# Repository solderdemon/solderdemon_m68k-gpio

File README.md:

# SolderDemon m68k GPIO

## Overview

A SolderDemon m68k expansion card with 32 GPIO lines at 5 V logic levels in four 8-bit ports. Two right-angle headers expose the signals, and three ATF1502AS CPLDs handle bus decoding and port control.

J1 matches the expansion bus pinout of [rosco_m68k r2](https://github.com/rosco-m68k/rosco_m68k). The original rosco_m68k project was created by Ross Bamford, The Really Old-School Company Limited, and contributors.

**Status.** r1 fabrication files and CPLD programming files are available. Hardware verification is pending.

## Start here

- [KiCad project](design/solderdemon_m68k-gpio.kicad_pro)
- [Schematic (PDF)](manufacturing/solderdemon_m68k-gpio-schematic.pdf)
- [Assembly and bring-up](docs/BRINGUP.md)
- [Gerbers and drill files](manufacturing/solderdemon_m68k-gpio-fab.zip)

## Board views

| Top | Bottom |
|:---:|:---:|
|  |  |

## Hardware

### Features

| | |
|---|---|
| Registers | `$F40001` A, `$F40003` B, `$F40005` direction, `$F40007` C, `$F40009` D; byte access only |
| Logic | 3 × ATF1502AS-10JU44 in PLCC-44 sockets, programmed in one J4 JTAG chain; BAT85 diode for DTACK |
| Ports | registered CPLD outputs, tristated by the direction register; readback senses the header pins |
| Direction | per 8-pin port |
| Pull-ups | 10 kΩ on every pin (4 × SIP-9 arrays) |
| Power | 5 V from the bus |
| Assembly | through-hole only, 3 × PLCC-44 sockets, CPLDs need JEDEC files and a JTAG programmer |
| Size | 86 × 96 mm, 2 layers |

### J2 / J3 connectors

Two right-angle, unshrouded 2×10 pin headers, 2.54 mm pitch, in the original connector positions on the left edge. J2 is above J3. Pin 1 is marked on the PCB.

| Pins | J2 | J3 |
|---|---|---|
| 1–8 | A0–A7 (driver bits 0–7) | C0–C7 (bits 16–23) |
| 9–16 | B0–B7 (bits 8–15) | D0–D7 (bits 24–31) |
| 17, 19, 20 | GND | GND |
| 18 | +5V from the bus, no fuse | +5V from the bus, no fuse |

All VCC pins of U1–U3 connect to the bus +5 V rail. The CPLD output drive differs from the previous 74HCT574; size external loads to the ATF1502AS datasheet. The unshrouded headers have no key; check cable orientation before connecting an adapter.

### Registers

| Address | Write | Read |
|---|---|---|
| `$F40001` | port A output latch | port A pin levels |
| `$F40003` | port B output latch | port B pin levels |
| `$F40005` | direction: b0 A, b1 B, b2 C, b3 D; 1 = output | — |
| `$F40007` | port C output latch | port C pin levels |
| `$F40009` | port D output latch | port D pin levels |

System reset clears the direction register, so every pin starts as an input. Every byte (odd-address) cycle in `$F40000–$F41FFF` gets DTACK; unused addresses read as garbage, and even-address access ends in a bus error.

## Using the board

### Example

```c
#include "gpio.h"

gpio_init();                                        /* all inputs, latches 0 */
gpio_config(GPIO_DIR_A | GPIO_DIR_C, 0x00000000);   /* A and C outputs (low), B and D inputs */
gpio_write_pin(16, true);                           /* J3.1 (C0) = 5 V */
uint32_t in = gpio_read();                          /* B in bits 8..15, D in bits 24..31 */
```

`gpio_selftest()` drives every pin with test patterns and returns a mask of failed pins; run it with J2 and J3 disconnected.

`gpio_write_port(port, value)` and `gpio_read_port(port)` touch one 8-bit port (0..3 = A..D) with a single register access and leave the other ports alone.

For a PS/2 keyboard and mouse on J2 or J3, see the [GPIO PS/2 adapter](https://github.com/solderdemon/solderdemon_m68k-gpio-ps2).

## Build and verification

### Design files

| Path | Contents |
|---|---|
| `design/solderdemon_m68k-gpio.kicad_pro` / `.kicad_sch` / `.kicad_pcb` | KiCad 10 project |
| `solderdemon_m68k-gpio.kicad_sym`, `solderdemon_m68k-gpio.pretty/` | local CPLD/bus symbols, the J1 socket footprint and the SolderDemon logo |
| `code/firmware/cpld/gpio_decode.pld`, `gpio_ab.pld`, `gpio_cd.pld`, `build.sh` | ATF1502AS logic, pinouts and JEDEC builds |
| `logo.png` | logo source; `tools/make_logo.py` turns it into `SolderDemon_Logo` (same generator and size as on the busboard) |
| `manufacturing/` | r1 Gerbers, drill, fab zip, pos, BOM and schematic PDF |
| `code/software/` | driver `gpio.c/.h`, example `main.c`, Makefile |
| `code/tests/test_driver.c` | driver test against a model of the latches, direction register and pull-ups |
| `tools/build_card.py`, `tools/make_bus_footprint.py`, `tools/make_logo.py`, `tools/route_card.py`, `tools/cleanup_dangling.py` | schematic/PCB generation, J1 footprint, routing, router clean-up |
| `tools/cupl.py`, `tools/sim_card.py` | CUPL source interpreter and GPIO behavior checks |
| [docs/DESIGN.md](docs/DESIGN.md) | how the card works: addressing, bus cycles, DTACK diode, levels, power |
| [docs/TIMING.md](docs/TIMING.md) | worst-case bus timing against the MC68010 at 10 MHz, /DTACK level |
| [docs/BRINGUP.md](docs/BRINGUP.md) | assembly and first power-up |
| [docs/BUILD.md](docs/BUILD.md) | regenerating the files |

### Verification

- r1 schematic ERC: 0 violations; schematic/PCB parity: 0 issues.
- All three CPLD sources fit successfully with locked pins and JEDEC output (decoder 11/32 macrocells, each port CPLD 27/32). CUPL source simulation passes address decode, writes, reset and pin readback. ERC: 0 violations. Routed DRC: 0 violations, 0 unconnected pads, 0 schematic parity issues; 123 vias. Worst-case timing at 10 MHz: reads with zero wait states (/DTACK margin 75 ns, data margin 167 ns), writes with at most one; see docs/TIMING.md. The driver test models the register interface, but it does not verify the new CPLD fuse maps.
- Physical board and /DTACK level on an oscilloscope remain unverified.

<!-- repository-layout -->
## Repository layout

- [`design/`](design/solderdemon_m68k-gpio.kicad_pro): KiCad project, schematic sheets, PCB, local libraries and design data. Open the project directly here.
- [`code/firmware/`](code/firmware/): ROM and programmable-logic sources and programming files.
- [`code/software/`](code/software/): drivers, examples and applications.
- [`code/build/`](code/build/): local build products; ignored by Git except for its README.
- [`tools/`](tools/): generators, simulations and export scripts. Run commands from the repository root unless stated otherwise.
- [`manufacturing/`](manufacturing/): fabrication packages.

Programmable-logic files are in `code/firmware/cpld/`. Native CPLD tools retain their adjacent `bin/` outputs.
Design files and documentation are generated by scripts in `tools/`; change the sources and regenerate. Keep `.kicad_pro` as the source of DRC rules.
<!-- /repository-layout -->

## Licences and attribution

Copyright © 2026 SolderDemon.

No project-wide licence has been specified.

Hardware and driver by Mykhailo.

Third-party materials retain their original notices and licence terms.

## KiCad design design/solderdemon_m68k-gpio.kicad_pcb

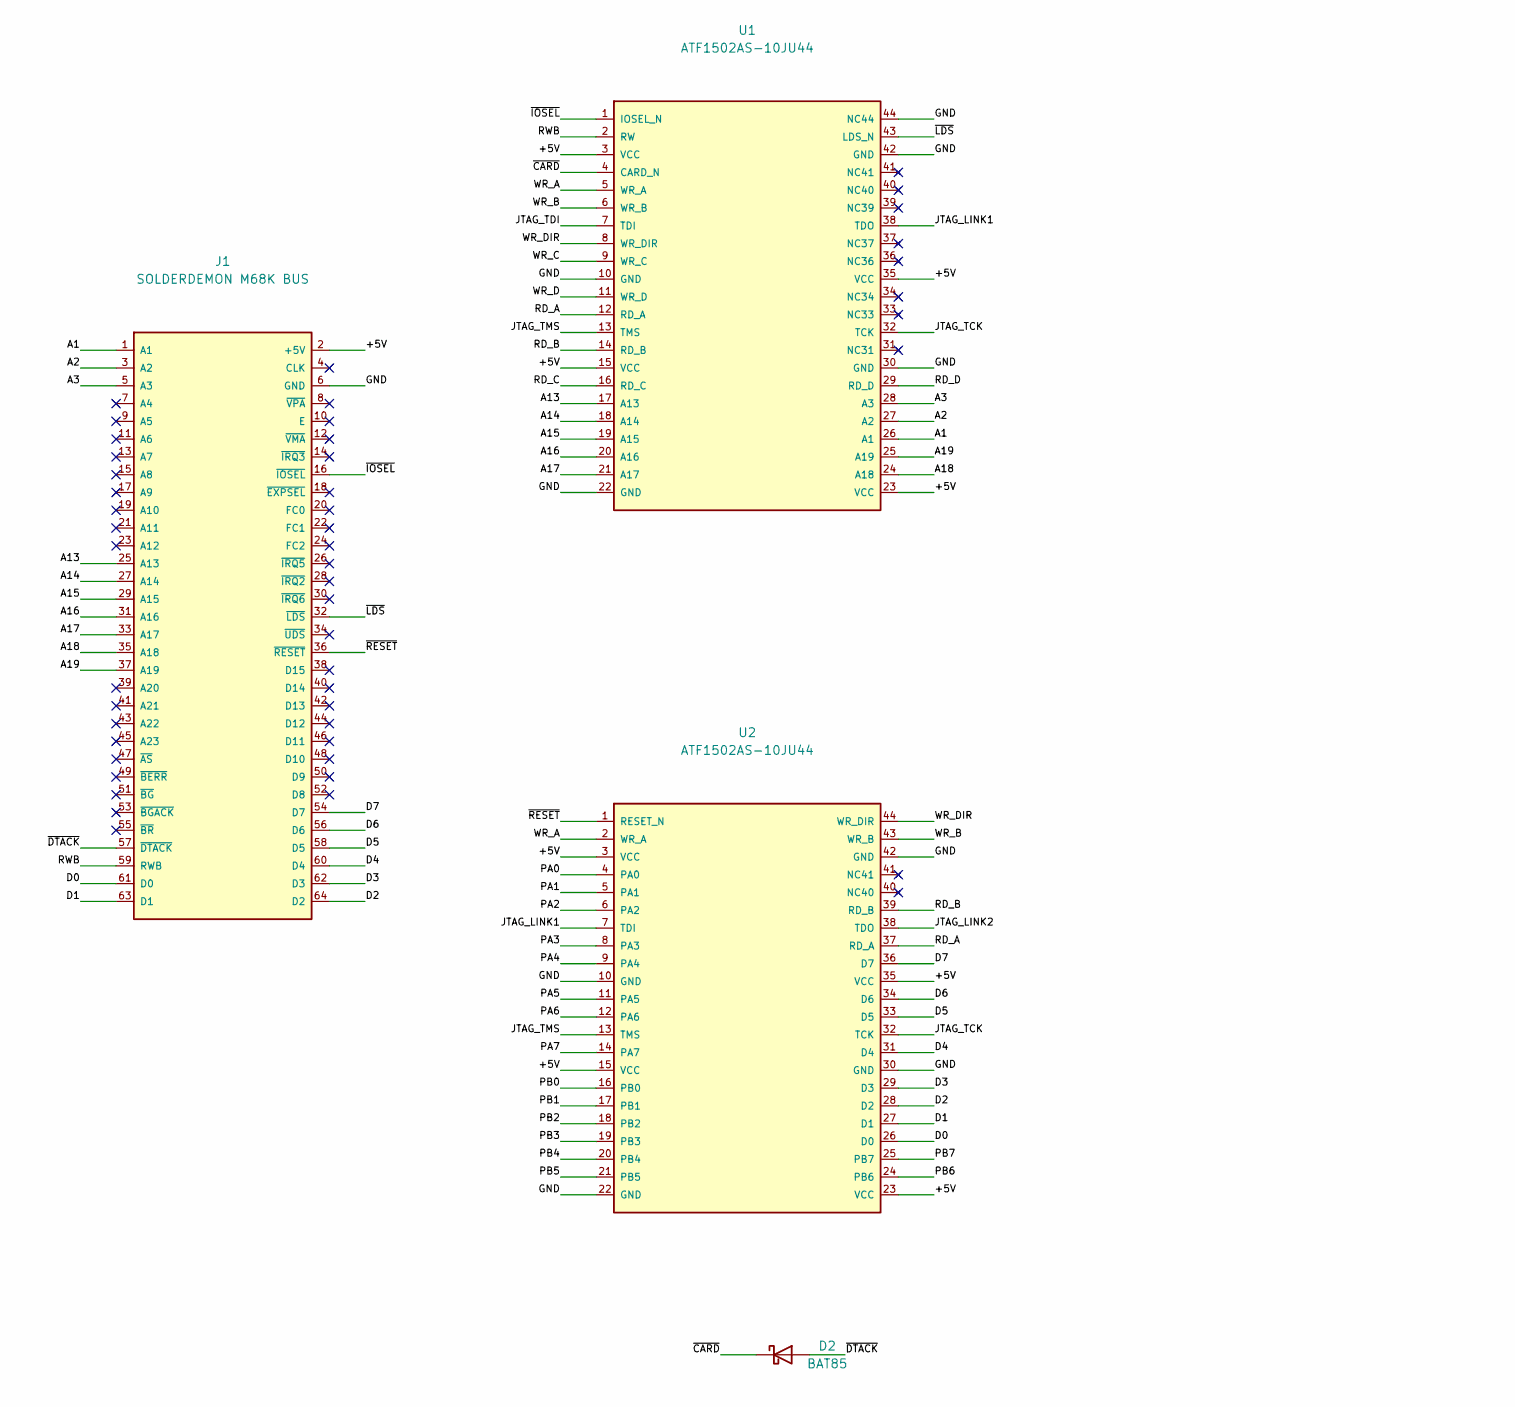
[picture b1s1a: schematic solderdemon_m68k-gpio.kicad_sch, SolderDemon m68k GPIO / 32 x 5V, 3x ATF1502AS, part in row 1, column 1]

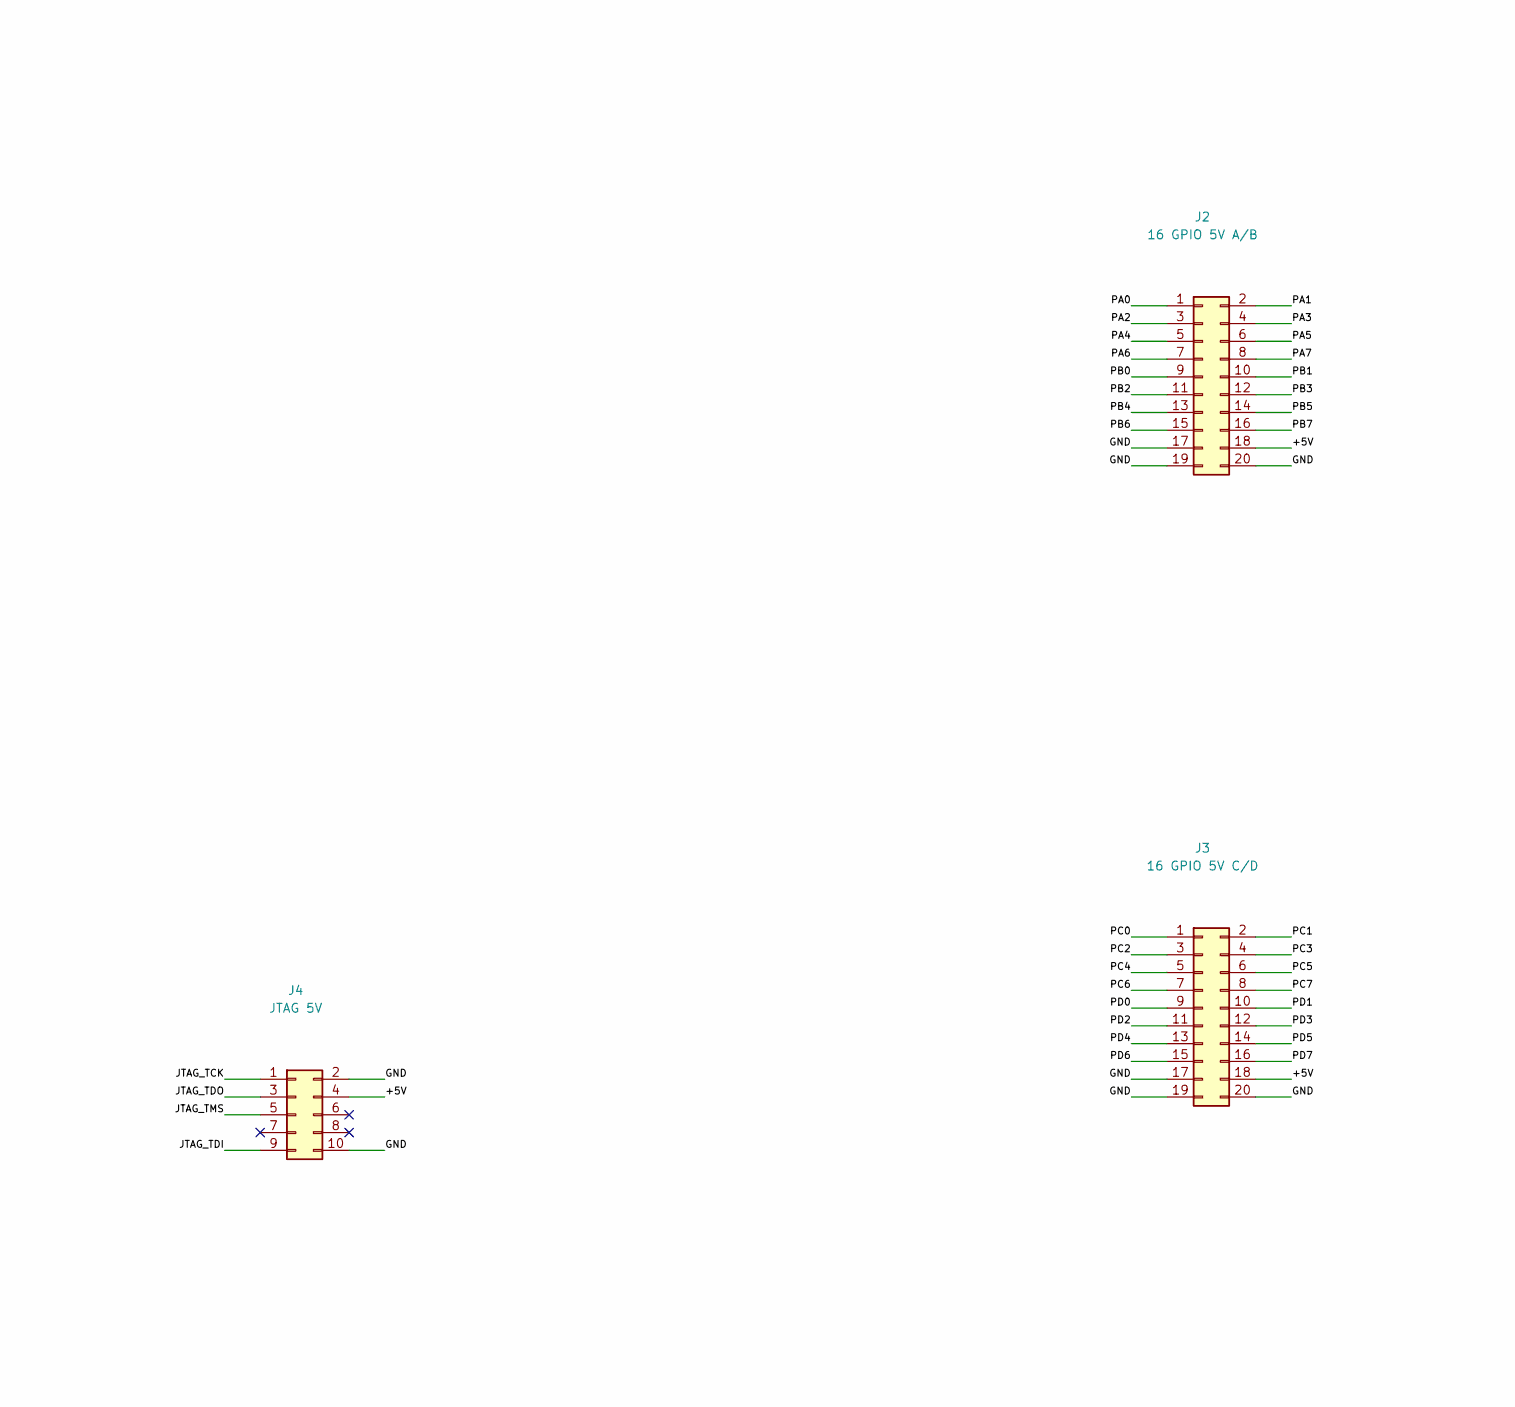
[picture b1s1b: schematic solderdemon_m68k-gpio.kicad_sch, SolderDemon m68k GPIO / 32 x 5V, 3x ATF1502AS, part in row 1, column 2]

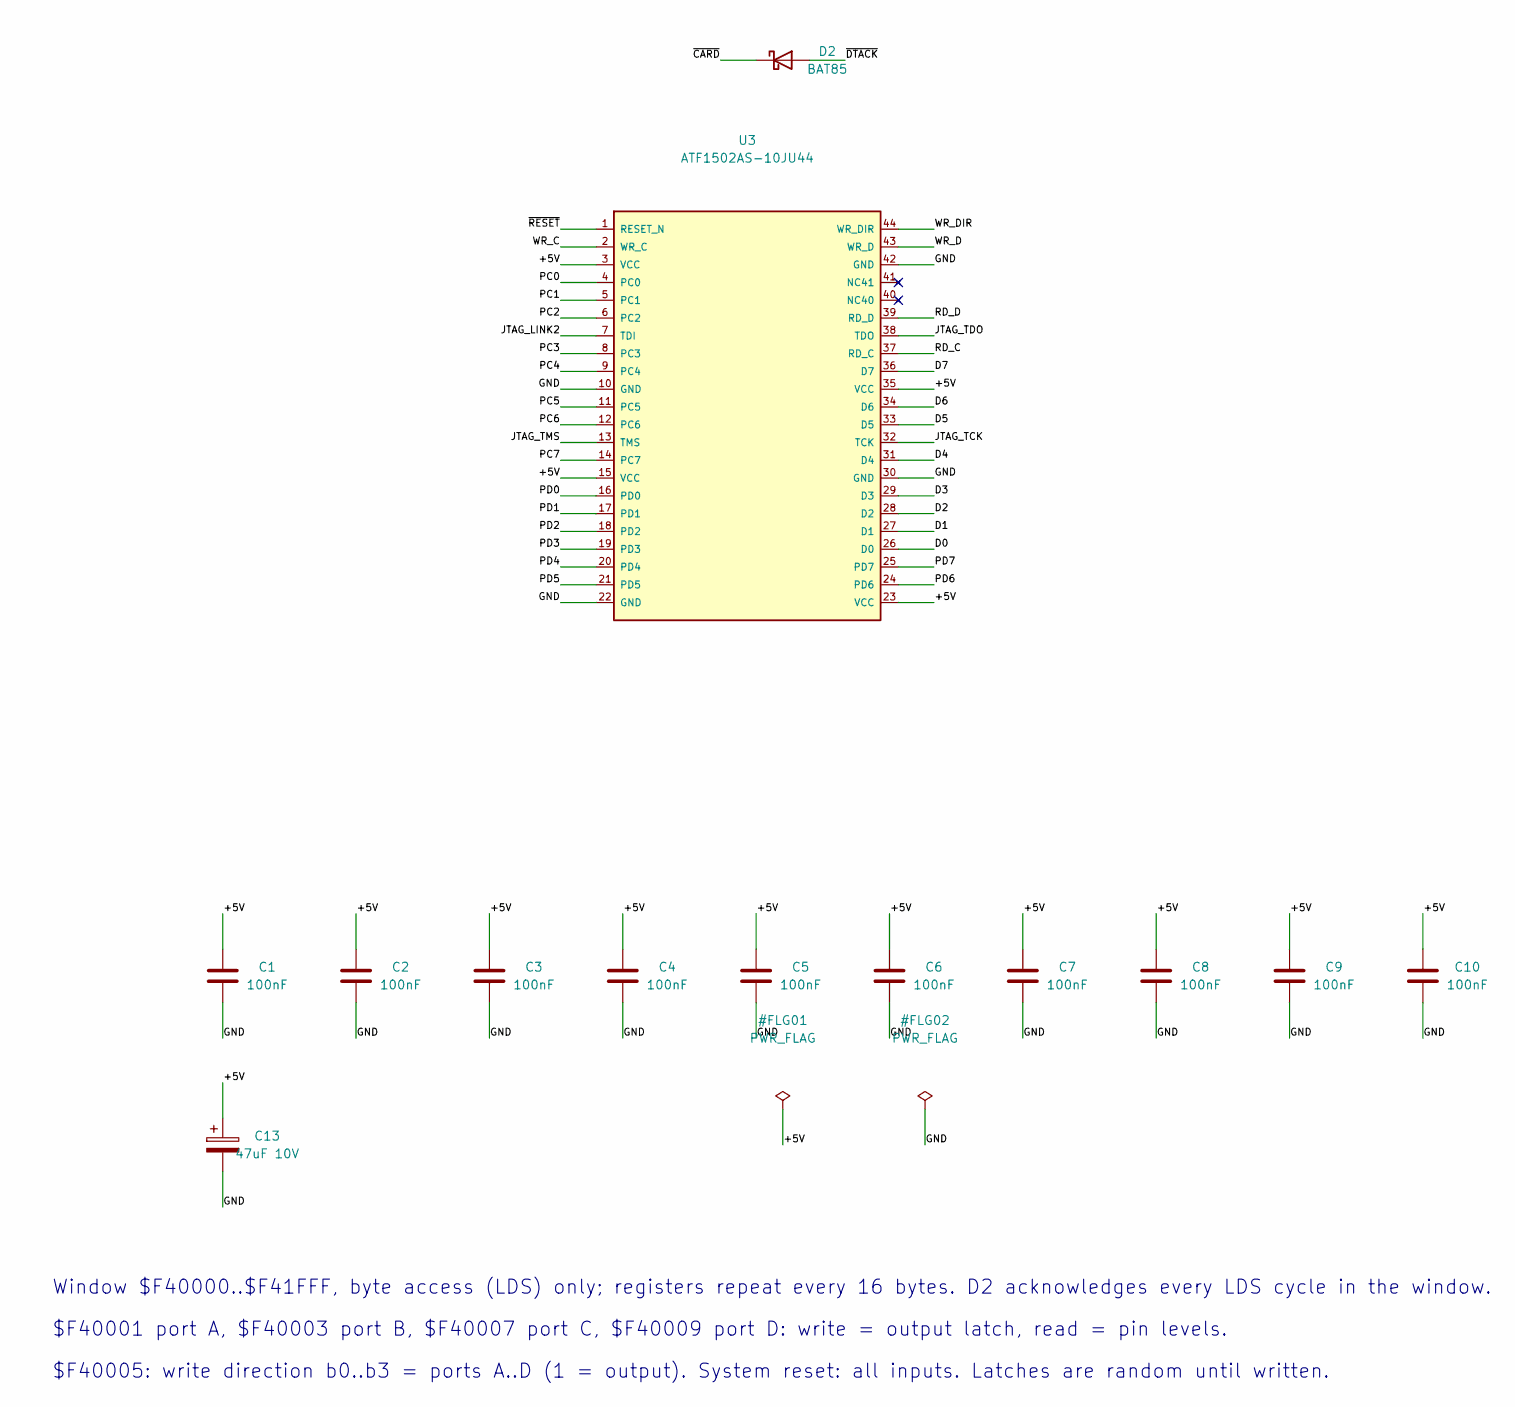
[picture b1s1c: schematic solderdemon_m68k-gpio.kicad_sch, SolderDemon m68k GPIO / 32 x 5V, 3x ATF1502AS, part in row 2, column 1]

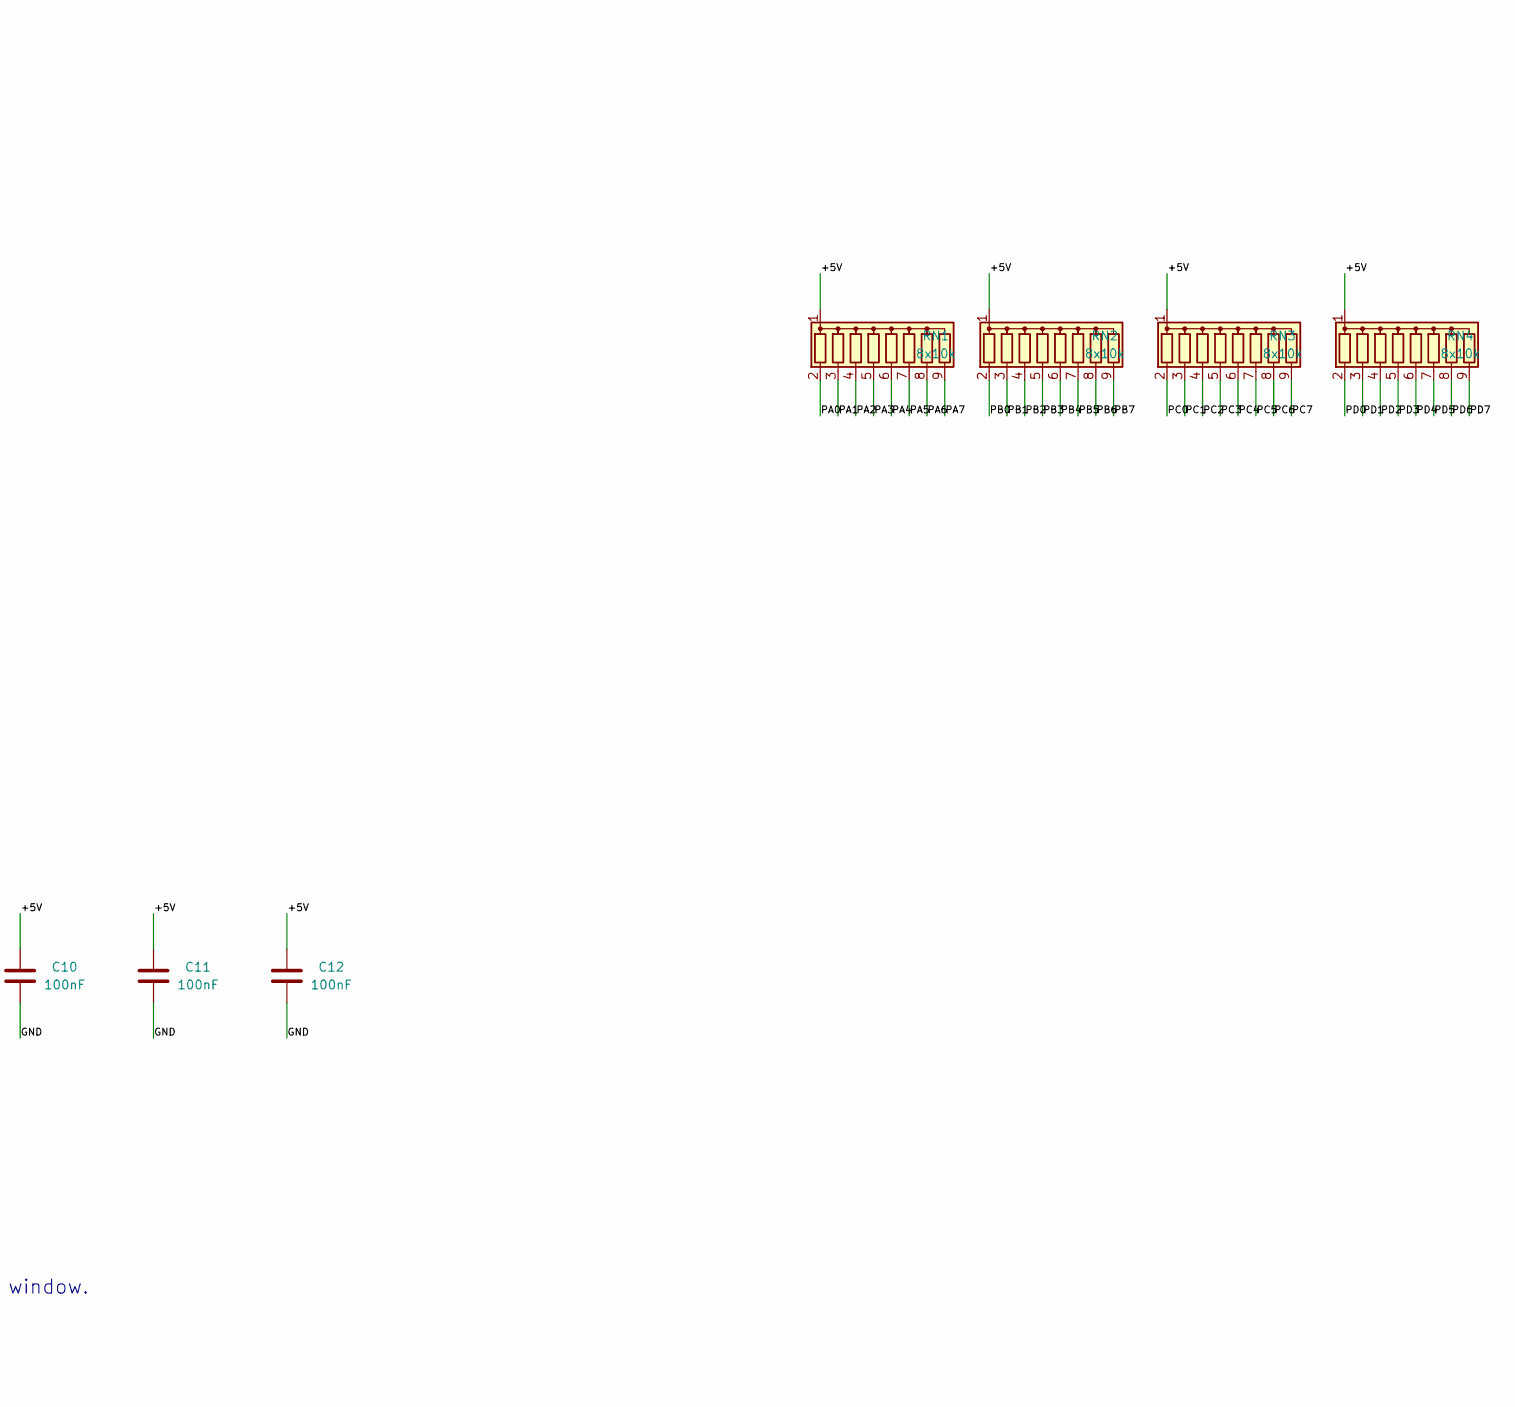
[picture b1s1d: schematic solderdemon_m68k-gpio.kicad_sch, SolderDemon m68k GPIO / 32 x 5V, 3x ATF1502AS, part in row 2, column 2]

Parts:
C1, C2, C3, C4, C5, C6, C7, C8, C9, C10, C11, C12: 100nF; C_Radial_5.08mm
C13: 47uF 10V; CP_Radial_D6.3mm_P2.50mm
D2: BAT85; D_DO-35_SOD27_P7.62mm_Horizontal
J1: SOLDERDEMON M68K BUS; PinSocket_2x32_P2.54mm_Horizontal_CardEdge
J2: 16 GPIO 5V A/B; PinHeader_2x10_P2.54mm_Horizontal
J3: 16 GPIO 5V C/D; PinHeader_2x10_P2.54mm_Horizontal
J4: JTAG 5V; PinHeader_2x05_P2.54mm_Vertical
RN1, RN2, RN3, RN4: 8x10k; R_Array_SIP9
U1, U2, U3: ATF1502AS-10JU44; PLCC-44_THT-Socket

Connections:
/+5V: C1.1, C2.1, C3.1, C4.1, C5.1, C6.1, C7.1, C8.1, C9.1, C10.1, C11.1, C12.1, C13.1, J1.2 (+5V), J2.18, J3.18, J4.4, RN1.1 (common), RN2.1 (common), RN3.1 (common), RN4.1 (common), U1.3 (VCC), U1.15 (VCC), U1.23 (VCC), U1.35 (VCC), U2.3 (VCC), U2.15 (VCC), U2.23 (VCC), U2.35 (VCC), U3.3 (VCC), U3.15 (VCC), U3.23 (VCC), U3.35 (VCC)
/A1: J1.1 (A1), U1.26 (A1)
/A2: J1.3 (A2), U1.27 (A2)
/A3: J1.5 (A3), U1.28 (A3)
/A13: J1.25 (A13), U1.17 (A13)
/A14: J1.27 (A14), U1.18 (A14)
/A15: J1.29 (A15), U1.19 (A15)
/A16: J1.31 (A16), U1.20 (A16)
/A17: J1.33 (A17), U1.21 (A17)
/A18: J1.35 (A18), U1.24 (A18)
/A19: J1.37 (A19), U1.25 (A19)
/D0: J1.61 (D0), U2.26 (D0), U3.26 (D0)
/D1: J1.63 (D1), U2.27 (D1), U3.27 (D1)
/D2: J1.64 (D2), U2.28 (D2), U3.28 (D2)
/D3: J1.62 (D3), U2.29 (D3), U3.29 (D3)
/D4: J1.60 (D4), U2.31 (D4), U3.31 (D4)
/D5: J1.58 (D5), U2.33 (D5), U3.33 (D5)
/D6: J1.56 (D6), U2.34 (D6), U3.34 (D6)
/D7: J1.54 (D7), U2.36 (D7), U3.36 (D7)
/GND: C1.2, C2.2, C3.2, C4.2, C5.2, C6.2, C7.2, C8.2, C9.2, C10.2, C11.2, C12.2, C13.2, J1.6 (GND), J2.17, J2.19, J2.20, J3.17, J3.19, J3.20, J4.2, J4.10, U1.10 (GND), U1.22 (GND), U1.30 (GND), U1.42 (GND), U1.44 (NC44), U2.10 (GND), U2.22 (GND), U2.30 (GND), U2.42 (GND), U3.10 (GND), U3.22 (GND), U3.30 (GND), U3.42 (GND)
/JTAG_LINK1: U1.38 (TDO), U2.7 (TDI)
/JTAG_LINK2: U2.38 (TDO), U3.7 (TDI)
/JTAG_TCK: J4.1, U1.32 (TCK), U2.32 (TCK), U3.32 (TCK)
/JTAG_TDI: J4.9, U1.7 (TDI)
/JTAG_TDO: J4.3, U3.38 (TDO)
/JTAG_TMS: J4.5, U1.13 (TMS), U2.13 (TMS), U3.13 (TMS)
/PA0: J2.1, RN1.2 (R1), U2.4 (PA0)
/PA1: J2.2, RN1.3 (R2), U2.5 (PA1)
/PA2: J2.3, RN1.4 (R3), U2.6 (PA2)
/PA3: J2.4, RN1.5 (R4), U2.8 (PA3)
/PA4: J2.5, RN1.6 (R5), U2.9 (PA4)
/PA5: J2.6, RN1.7 (R6), U2.11 (PA5)
/PA6: J2.7, RN1.8 (R7), U2.12 (PA6)
/PA7: J2.8, RN1.9 (R8), U2.14 (PA7)
/PB0: J2.9, RN2.2 (R1), U2.16 (PB0)
/PB1: J2.10, RN2.3 (R2), U2.17 (PB1)
/PB2: J2.11, RN2.4 (R3), U2.18 (PB2)
/PB3: J2.12, RN2.5 (R4), U2.19 (PB3)
/PB4: J2.13, RN2.6 (R5), U2.20 (PB4)
/PB5: J2.14, RN2.7 (R6), U2.21 (PB5)
/PB6: J2.15, RN2.8 (R7), U2.24 (PB6)
/PB7: J2.16, RN2.9 (R8), U2.25 (PB7)
/PC0: J3.1, RN3.2 (R1), U3.4 (PC0)
/PC1: J3.2, RN3.3 (R2), U3.5 (PC1)
/PC2: J3.3, RN3.4 (R3), U3.6 (PC2)
/PC3: J3.4, RN3.5 (R4), U3.8 (PC3)
/PC4: J3.5, RN3.6 (R5), U3.9 (PC4)
/PC5: J3.6, RN3.7 (R6), U3.11 (PC5)
/PC6: J3.7, RN3.8 (R7), U3.12 (PC6)
/PC7: J3.8, RN3.9 (R8), U3.14 (PC7)
/PD0: J3.9, RN4.2 (R1), U3.16 (PD0)
/PD1: J3.10, RN4.3 (R2), U3.17 (PD1)
/PD2: J3.11, RN4.4 (R3), U3.18 (PD2)
/PD3: J3.12, RN4.5 (R4), U3.19 (PD3)
/PD4: J3.13, RN4.6 (R5), U3.20 (PD4)
/PD5: J3.14, RN4.7 (R6), U3.21 (PD5)
/PD6: J3.15, RN4.8 (R7), U3.24 (PD6)
/PD7: J3.16, RN4.9 (R8), U3.25 (PD7)
/RD_A: U1.12 (RD_A), U2.37 (RD_A)
/RD_B: U1.14 (RD_B), U2.39 (RD_B)
/RD_C: U1.16 (RD_C), U3.37 (RD_C)
/RD_D: U1.29 (RD_D), U3.39 (RD_D)
/RWB: J1.59 (RWB), U1.2 (RW)
/WR_A: U1.5 (WR_A), U2.2 (WR_A)
/WR_B: U1.6 (WR_B), U2.43 (WR_B)
/WR_C: U1.9 (WR_C), U3.2 (WR_C)
/WR_D: U1.11 (WR_D), U3.43 (WR_D)
/WR_DIR: U1.8 (WR_DIR), U2.44 (WR_DIR), U3.44 (WR_DIR)
/~CARD: D2.1 (K), U1.4 (CARD_N)
/~DTACK: D2.2 (A), J1.57 (~DTACK)
/~IOSEL: J1.16 (~IOSEL), U1.1 (IOSEL_N)
/~LDS: J1.32 (~LDS), U1.43 (LDS_N)
/~RESET: J1.36 (~RESET), U2.1 (RESET_N), U3.1 (RESET_N)

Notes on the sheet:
Window $F40000..$F41FFF, byte access (LDS) only; registers repeat every 16 bytes. D2 acknowledges every LDS cycle in the window.
$F40001 port A, $F40003 port B, $F40007 port C, $F40009 port D: write = output latch, read = pin levels.
$F40005: write direction b0..b3 = ports A..D (1 = output). System reset: all inputs. Latches are random until written.

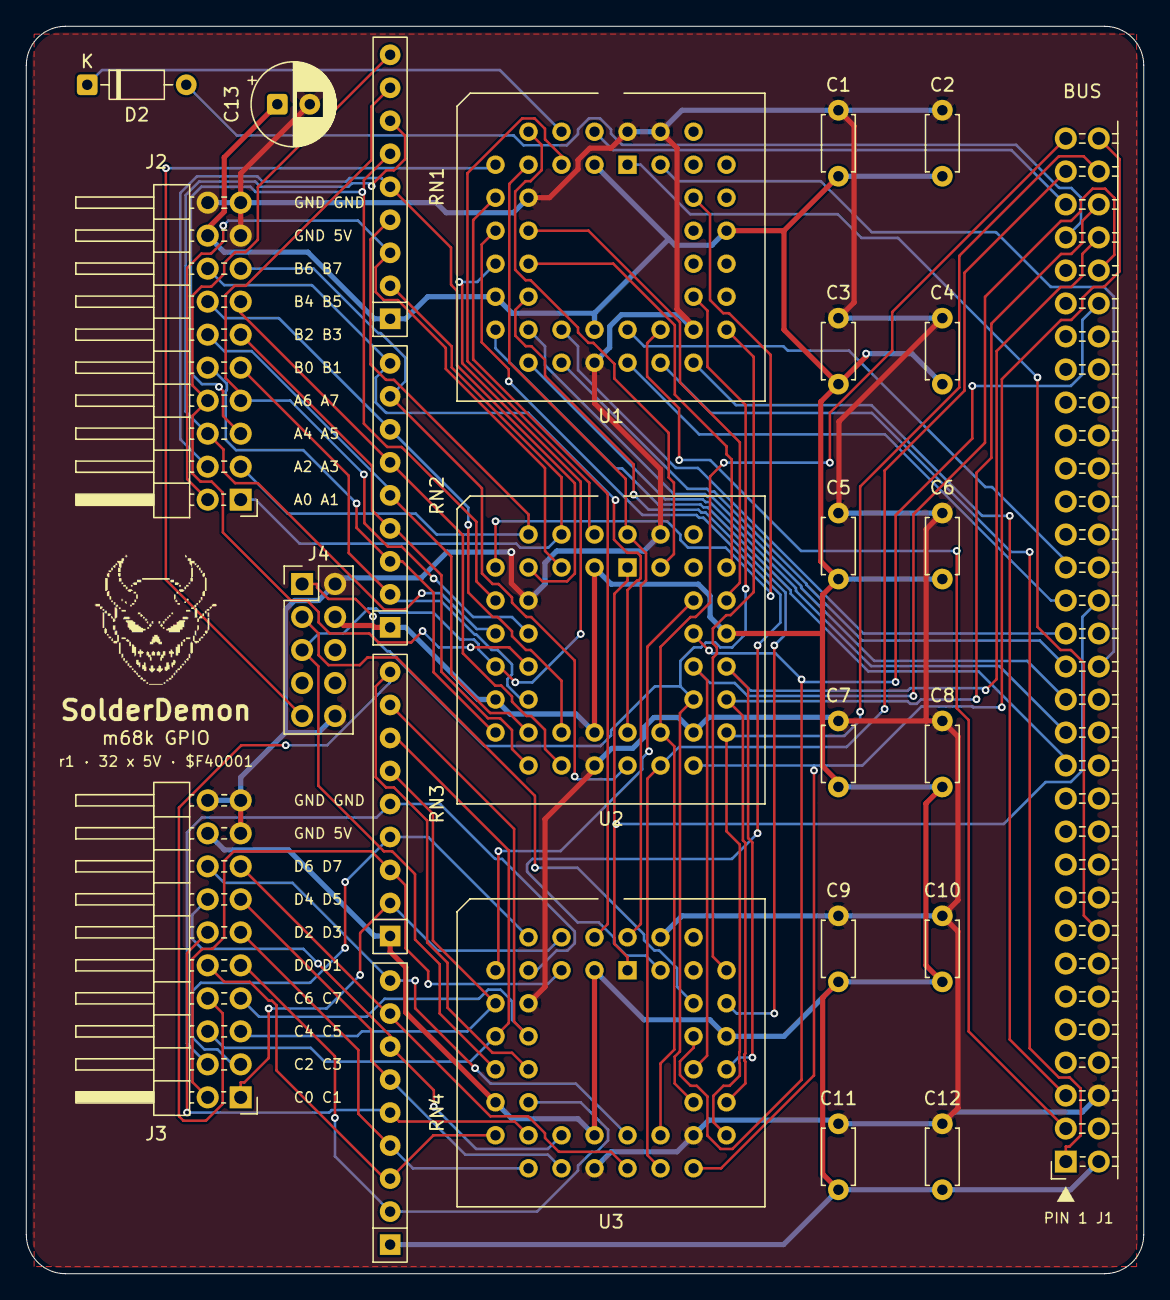
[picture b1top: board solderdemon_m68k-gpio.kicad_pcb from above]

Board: 2 copper layers, 86.0 x 96.0 mm, 26 parts (0 on the bottom side), 73 nets.

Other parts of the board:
LOGO1: SolderDemon_Logo

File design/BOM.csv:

Reference,Value,Footprint
J1,SOLDERDEMON M68K BUS,solderdemon_m68k-gpio:PinSocket_2x32_P2.54mm_Horizontal_CardEdge
U1,ATF1502AS-10JU44,Package_LCC:PLCC-44_THT-Socket
U2,ATF1502AS-10JU44,Package_LCC:PLCC-44_THT-Socket
U3,ATF1502AS-10JU44,Package_LCC:PLCC-44_THT-Socket
D2,BAT85,Diode_THT:D_DO-35_SOD27_P7.62mm_Horizontal
J4,JTAG 5V,Connector_PinHeader_2.54mm:PinHeader_2x05_P2.54mm_Vertical
RN1,8x10k,Resistor_THT:R_Array_SIP9
RN2,8x10k,Resistor_THT:R_Array_SIP9
RN3,8x10k,Resistor_THT:R_Array_SIP9
RN4,8x10k,Resistor_THT:R_Array_SIP9
J2,16 GPIO 5V A/B,Connector_PinHeader_2.54mm:PinHeader_2x10_P2.54mm_Horizontal
J3,16 GPIO 5V C/D,Connector_PinHeader_2.54mm:PinHeader_2x10_P2.54mm_Horizontal
C1,100nF,SolderDemonCaps:C_Radial_5.08mm
C2,100nF,SolderDemonCaps:C_Radial_5.08mm
C3,100nF,SolderDemonCaps:C_Radial_5.08mm
C4,100nF,SolderDemonCaps:C_Radial_5.08mm
C5,100nF,SolderDemonCaps:C_Radial_5.08mm
C6,100nF,SolderDemonCaps:C_Radial_5.08mm
C7,100nF,SolderDemonCaps:C_Radial_5.08mm
C8,100nF,SolderDemonCaps:C_Radial_5.08mm
C9,100nF,SolderDemonCaps:C_Radial_5.08mm
C10,100nF,SolderDemonCaps:C_Radial_5.08mm
C11,100nF,SolderDemonCaps:C_Radial_5.08mm
C12,100nF,SolderDemonCaps:C_Radial_5.08mm
C13,47uF 10V,Capacitor_THT:CP_Radial_D6.3mm_P2.50mm
